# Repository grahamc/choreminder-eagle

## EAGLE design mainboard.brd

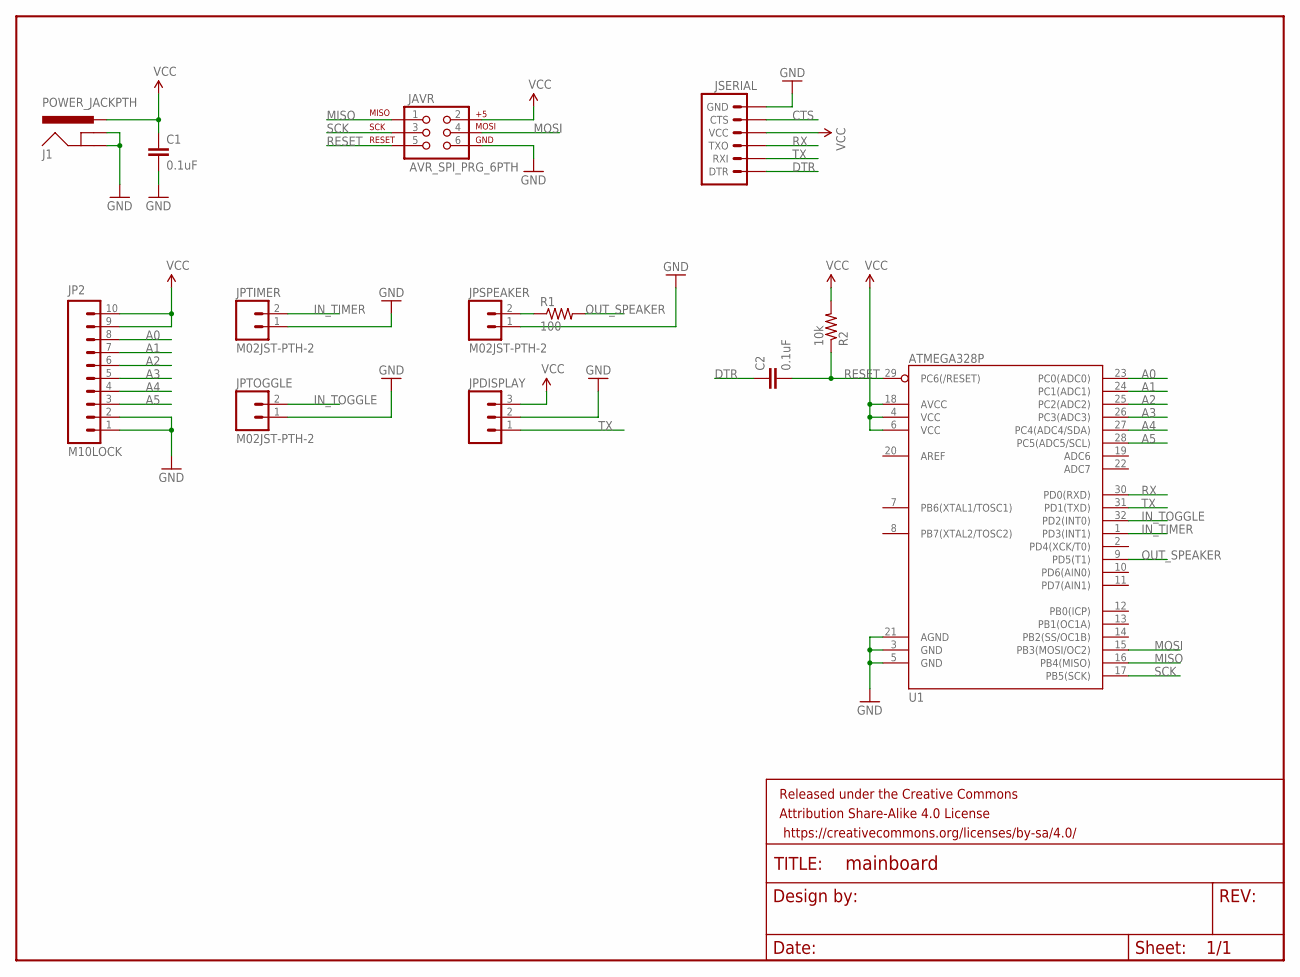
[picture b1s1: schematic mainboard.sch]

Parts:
C1, C2: 0.1uF; 0603-CAP
FRAME1: FRAME-LETTER; CREATIVE_COMMONS
J1: POWER_JACKPTH; POWER_JACK_PTH
JAVR: AVR_SPI_PRG_6PTH; 2X3
JP2: M10LOCK; 1X10_LOCK
JPDISPLAY: M03JST-PTH; JST-3-PTH
JPSPEAKER: M02JST-PTH-2; JST-2-PTH
JPTIMER: M02JST-PTH-2; JST-2-PTH
JPTOGGLE: M02JST-PTH-2; JST-2-PTH
JSERIAL: ARDUINO_SERIAL_PROGRAMPTH; 1X06
R1: 100; 0603-RES
R2: 10k; 0603-RES
U1: ATMEGA328P; TQFP32-08

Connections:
A0: JP2.8, U1.23 (PC0(ADC0))
A1: JP2.7, U1.24 (PC1(ADC1))
A2: JP2.6, U1.25 (PC2(ADC2))
A3: JP2.5, U1.26 (PC3(ADC3))
A4: JP2.4, U1.27 (PC4(ADC4/SDA))
A5: JP2.3, U1.28 (PC5(ADC5/SCL))
CTS: JSERIAL.5 (CTS)
DTR: C2.1, JSERIAL.1 (DTR)
GND: C1.2, J1.GND, J1.GNDBREAK, JAVR.6, JP2.1, JP2.2, JPDISPLAY.2, JPSPEAKER.1, JPTIMER.1, JPTOGGLE.1, JSERIAL.6 (GND), U1.3 (GND), U1.5 (GND), U1.21 (AGND)
IN_TIMER: JPTIMER.2, U1.1 (PD3(INT1))
IN_TOGGLE: JPTOGGLE.2, U1.32 (PD2(INT0))
MISO: JAVR.1, U1.16 (PB4(MISO))
MOSI: JAVR.4, U1.15 (PB3(MOSI/OC2))
unnamed: JPSPEAKER.2, R1.1
OUT_SPEAKER: R1.2, U1.9 (PD5(T1))
RESET: C2.2, JAVR.5, R2.1, U1.29 (PC6(/RESET))
RX: JSERIAL.3 (TXO), U1.30 (PD0(RXD))
SCK: JAVR.3, U1.17 (PB5(SCK))
TX: JPDISPLAY.1, JSERIAL.2 (RXI), U1.31 (PD1(TXD))
VCC: C1.1, J1.PWR, JAVR.2, JP2.9, JP2.10, JPDISPLAY.3, JSERIAL.4 (VCC), R2.2, U1.4 (VCC), U1.6 (VCC), U1.18 (AVCC)

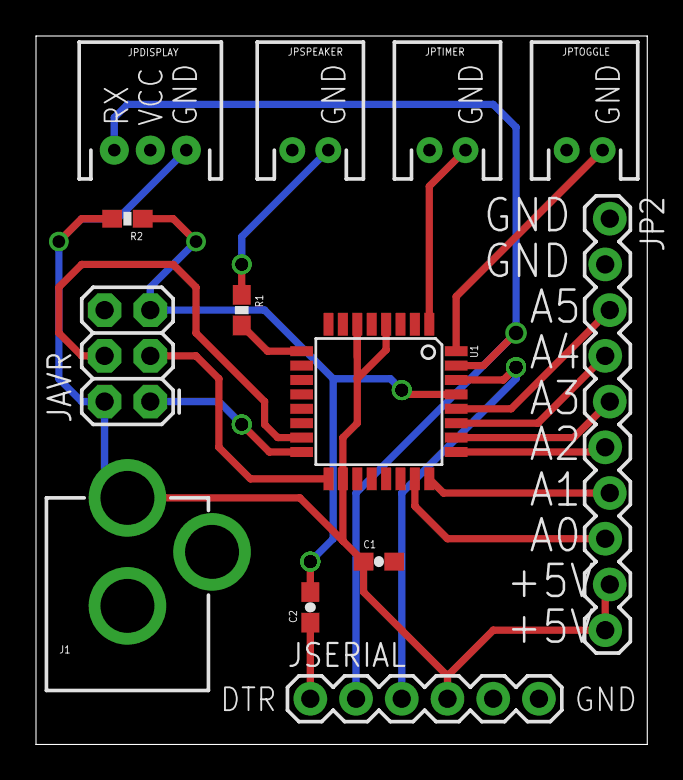
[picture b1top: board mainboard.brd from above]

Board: 2 copper layers, 34.0 x 39.4 mm, 14 parts (0 on the bottom side), 19 nets.

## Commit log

2014-04-12 initial import

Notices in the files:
mainboard.brd:
License: Creative Commons S-A
parts and their libraries:
SparkFun-Connectors: Licensing: Creative Commons ShareAlike 4.0 International - https://creativecommons.org/licenses/by-sa/4.0
SparkFun-Aesthetics: Released under the Creative Commons Attribution Share-Alike 4.0 License
SparkFun-Aesthetics: https://creativecommons.org/licenses/by-sa/4.0
